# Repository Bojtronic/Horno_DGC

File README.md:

# 🔥 Sistema de Automatización para Horno Eléctrico

El sistema ha sido desarrollado utilizando **ESP32, diseño de PCB en KiCad y una interfaz web**, permitiendo la **supervisión de sensores y control de actuadores en tiempo real**.

Este documento describe paso a paso cómo configurar el entorno de desarrollo, entender la arquitectura del sistema y ejecutar la aplicación.

El proyecto se encuentra en una etapa inicial y toma como referencia el Trabajo Final de Graduación (TFG) de Manuel Bojorge.

---

## 📦 Requisitos

### Hardware
- **ESP32**
- PCB diseñado en **KiCad**
- Sensores:
  - Temperatura
  - Corriente
  - Señales analógicas (voltaje DC variable)
- Actuadores:
  - Relés (contactos secos)
  - Etapa de potencia con IGBT (PWM)

---

### Software

#### 🔹 Arduino IDE
Entorno para programar el ESP32.

Verificar instalación:
```bash
arduino --version
```

Descarga: https://www.arduino.cc/en/software

---

#### 🔹 KiCad
Software para diseño de esquemas y PCB.

Descarga: https://www.kicad.org/

---

#### 🔹 Visual Studio Code
Editor recomendado para:
- Edición de código
- Control de versiones
- Manejo del proyecto

Descarga: https://code.visualstudio.com/

---

#### 🔹 Git (opcional)
Para control de versiones.

Verificar:
```bash
git --version
```

Descarga: https://git-scm.com/

---

### Sistema Operativo
- **Windows 10 / 11** (recomendado)

---

## 📥 1. Estructura del Proyecto

El proyecto se divide en tres componentes principales:

| Componente | Descripción |
|----------|------------|
| Hardware (PCB) | Diseño electrónico en KiCad |
| Firmware (ESP32) | Control de entradas y salidas |
| Interfaz Web | Visualización y control remoto |

---

## 🧩 2. Diseño del Hardware (PCB)

El diseño del PCB se realiza en **KiCad** e incluye:

### 🔹 Entradas digitales
- Tipo: **contacto seco**
- Conversión a nivel lógico:
  - **3.3V → 1 lógico**
  - **< 1.7V → 0 lógico**

Permiten detectar:
- Estados ON/OFF externos
- Sensores digitales

---

### 🔹 Entradas analógicas
- Señales de **voltaje DC variable**
- Usadas para:
  - Sensores de temperatura
  - Sensores de corriente
  - Otras variables físicas

---

### 🔹 Salidas digitales (Relés)
- Control de **contactos secos**
- Permiten manejar:
  - **120 VAC**
  - **240 VAC**

Aplicaciones:
- Encendido/apagado del horno
- Control de resistencias
- Activación de sistemas auxiliares

---

### 🔹 Salidas analógicas (voltaje variable)
- Rango:
  - **0V – 3.3V DC (ESP32)**
- Amplificación:
  - Hasta **12V DC**

Estas señales se exponen en terminales del PCB para controlar:
- Drivers externos
- Módulos de potencia

---

### 🔹 Control PWM con IGBT
- Generación de señal **PWM desde el ESP32**
- Etapa de potencia:
  - Driver de **IGBT**
- Permite:
  - Control fino de potencia del horno
  - Regulación de temperatura

---

## 🧠 3. Arquitectura del Sistema

El sistema funciona bajo el siguiente flujo:

1. La **interfaz web** envía comandos
2. El **ESP32 recibe las solicitudes**
3. El microcontrolador:
   - Procesa entradas
   - Controla salidas
4. Se actualizan los valores en la interfaz

---

## 🌐 4. Interfaz Web

La aplicación web permite:

### 🔹 Monitoreo
- Temperatura
- Corriente
- Voltajes
- Estados digitales

---

### 🔹 Control
- Activación/desactivación de relés
- Control de salidas analógicas
- Ajuste de parámetros de operación

---

### 🔹 Comunicación
- La interfaz envía comandos al ESP32
- El ESP32 responde con datos en tiempo real

---

## ⚙️ 5. Programación del ESP32

Abrir el proyecto en **Arduino IDE**

Seleccionar:
- Placa: ESP32
- Puerto correspondiente

Compilar y cargar:

```bash
Upload
```

El firmware se encarga de:

- Leer entradas digitales y analógicas
- Generar señales PWM
- Controlar relés
- Comunicarse con la interfaz web

---

## ▶️ 6. Ejecución del Sistema

1. Energizar el PCB
2. Conectar el ESP32 a la red
3. Acceder a la interfaz web (según configuración de red)

Desde la interfaz se puede:

- Ver datos en tiempo real
- Controlar el horno
- Ajustar parámetros

---

## 🏗 7. Flujo de Desarrollo

### 🔹 Hardware
- Diseño esquemático en KiCad
- Diseño de PCB
- Fabricación y pruebas

---

### 🔹 Firmware
- Desarrollo en Arduino IDE
- Pruebas de entradas/salidas
- Integración con hardware

---

### 🔹 Software
- Desarrollo de interfaz web
- Integración con ESP32
- Pruebas de comunicación

---

## 🛡 Reglas importantes

- ❌ No conectar cargas AC sin aislamiento adecuado
- ❌ No exceder voltajes de entrada del ESP32 (3.3V)
- ❌ Verificar conexiones antes de energizar

- ⚠ Manejar con precaución:
  - 120 VAC / 240 VAC
  - Etapas de potencia con IGBT

---

## 🚧 Estado del proyecto

- ✔ Diseño conceptual
- ✔ Definición de arquitectura
- ⚠ En desarrollo:
  - PCB
  - Firmware
  - Interfaz web

---

## 📌 Notas adicionales

Este proyecto toma como base el **TFG de Manuel Bojorge**, el cual sirve como referencia para:

- Arquitectura del sistema
- Diseño electrónico
- Integración hardware–software

---

## 📧 Soporte

Correo: **bojtronic@gmail.com**

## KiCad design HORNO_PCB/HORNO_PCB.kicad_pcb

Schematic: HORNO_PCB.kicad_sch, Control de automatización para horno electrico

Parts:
C5, C6, C8, C9: 10nF; C_Disc_D5.1mm_W3.2mm_P5.00mm
C7, C10: 100nF; C_Disc_D5.1mm_W3.2mm_P5.00mm
D1, D2, D3, D4, D9, D10, D11, D12, D13, D14: LED; LED_D4.0mm
F1: Fuse; Fuseholder_Cylinder-5x20mm_Schurter_0031_8201_Horizontal_Op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
Fuente_1: 12VDC; step_source
Fuente_2: 5VDC; step_source
Fuente_3: 3.3VDC; step_source
Fuente_4: -12VDC; step_source
J0_1: Alimentacion dispositivo serial; TerminalBlock_Phoenix_PT-1,5-3-5.0-H_1x03_P5.00mm_Horizontal
J0_2, J0_3, J0_4, J0_5, J0_6, J0_7, J0_8, J0_9, J0_10, J0_11, J0_12, J0_13, J0_14, J0_15, J0_16, J0_17, J0_18, J0_19: Terminales de tornillo espaciados en 5mm; TerminalBlock_Phoenix_PT-1,5-3-5.0-H_1x03_P5.00mm_Horizontal
J1: +5V +24V; TerminalBlock_MetzConnect_360271_1x01_Horizontal_ScrewM3.0_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
J7: 24VDC; TerminalBlock_Phoenix_PT-1,5-3-5.0-H_1x03_P5.00mm_Horizontal
J24, J25, J26, J27: Screw_Terminal_01x20; PinHeader_1x20_P2.54mm_Vertical
K1, K9: Relay 1; Relay_SPDT_Fujitsu_FTR-LYCA005x_FormC_Vertical
K2, K8: Relay 2; Relay_SPDT_Fujitsu_FTR-LYCA005x_FormC_Vertical
K7: Relay 3; Relay_SPDT_Fujitsu_FTR-LYCA005x_FormC_Vertical
Q1, Q2: 2N2222; TO-92
Q6, Q7: IRG4PF50W; TO-247-3_Vertical
R1, R2, R3, R4, R20, R26: 270Ω - 1/4 W; R_Axial_DIN0207_L6.3mm_D2.5mm_P10.16mm_Horizontal
R5, R6: 1 W; R_Axial_DIN0411_L9.9mm_D3.6mm_P15.24mm_Horizontal
R7, R8, R12, R28: 2.4 KΩ - 1/2 W; R_Axial_DIN0309_L9.0mm_D3.2mm_P15.24mm_Horizontal
R9, R10, R11, R44, R46, R48: 1 kΩ - 1/4 W; R_Axial_DIN0207_L6.3mm_D2.5mm_P10.16mm_Horizontal
R13, R16, R17, R18, R21, R22, R23, R24, R27, R29: Depende de la aplicación salida analógica; R_Axial_DIN0207_L6.3mm_D2.5mm_P10.16mm_Horizontal
R14, R15: 7.5KΩ - 1/4 W; R_Axial_DIN0207_L6.3mm_D2.5mm_P10.16mm_Horizontal
R19, R25: 10Ω - 1/4 W; R_Axial_DIN0207_L6.3mm_D2.5mm_P10.16mm_Horizontal
R37, R38: 39Ω - 1/4 W; R_Axial_DIN0207_L6.3mm_D2.5mm_P10.16mm_Horizontal
U1, U2, U3, U4: TLP521-1; DIP-4_W7.62mm
U9, U10, U17, U18: LM741; LM741_TH
U15, U19: TLP250; DIP-8_W7.62mm
U25: UDN2981A; DIP-18_W7.62mm_LongPads

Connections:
unnamed: D1.2 (A), R28.2
unnamed: D1.1 (K), U1.1
unnamed: D2.2 (A), R7.2
unnamed: D2.1 (K), U2.1
unnamed: D3.2 (A), R8.2
unnamed: D3.1 (K), U3.1
unnamed: D4.2 (A), R12.2
unnamed: D4.1 (K), U4.1
unnamed: D9.2 (A), R29.1
unnamed: D10.2 (A), R27.1
unnamed: C5.2, C6.2, C8.2, C9.2, C10.2, D9.1 (K), D10.1 (K), D11.1 (K), D12.1 (K), D13.1 (K), D14.1 (K), Fuente_1.2 (IN-), Fuente_1.3 (OUT-), Fuente_2.2 (IN-), Fuente_2.3 (OUT-), Fuente_3.2 (IN-), Fuente_3.3 (OUT-), Fuente_4.3 (OUT-), J0_5.3, J0_10.3, J0_13.2, J0_14.3, J0_18.3, J7.3, J25.20, K1.A2, K2.A2, K7.A2, K8.A2, K9.A2, Q6.3 (E), Q7.3 (E), R21.2, R23.2, R37.2, R38.2, U1.2, U1.3, U2.2, U2.3, U3.2, U3.3, U4.2, U4.3, U15.3 (C), U19.3 (C), U25.10 (GND)
unnamed: D11.2 (A), R18.1
unnamed: D12.2 (A), R17.1
unnamed: D13.2 (A), R16.1
unnamed: D14.2 (A), R13.1
unnamed: F1.1, Fuente_1.1 (IN+), Fuente_2.1 (IN+), Fuente_3.1 (IN+), J0_2.3, J0_11.3, J0_12.3, J0_15.3, U25.9 (Vs)
unnamed: Fuente_1.4 (OUT+), U9.7 (V+), U10.7 (V+), U15.8 (VCC), U17.7 (V+), U18.7 (V+), U19.8 (VCC)
unnamed: Fuente_2.4 (OUT+), J24.2, J25.19
unnamed: Fuente_3.4 (OUT+), J26.5, J26.11, J26.17, Q1.3 (C), Q2.3 (C), R1.2, R2.2, R3.2, R4.2
unnamed: Fuente_4.4 (OUT+), U9.4 (V-), U10.4 (V-), U15.5 (VEE), U17.4 (V-), U18.4 (V-), U19.5 (VEE)
unnamed: J0_1.1, J0_1.2, J0_1.3, J1.1
unnamed: J0_2.1, R28.1
unnamed: J0_3.1, J24.5
unnamed: J0_3.2, J24.6
unnamed: C7.2, J0_3.3, J24.1
unnamed: J0_4.1, K1.12
unnamed: J0_4.2, K1.11
unnamed: J0_4.3, K1.14
unnamed: C6.1, J0_5.1, U9.3 (+)
unnamed: C5.1, J0_5.2, U10.3 (+)
unnamed: J0_6.1, K2.12
unnamed: J0_6.2, K2.11
unnamed: J0_6.3, K2.14
unnamed: J0_7.1, K9.12
unnamed: J0_7.2, K9.11
unnamed: J0_7.3, K9.14
unnamed: J0_8.1, K8.12
unnamed: J0_8.2, K8.11
unnamed: J0_8.3, K8.14
unnamed: J0_9.1, K7.12
unnamed: J0_9.2, K7.11
unnamed: J0_9.3, K7.14
unnamed: J0_10.1, R29.2, U25.18 (O1)
unnamed: J0_11.1, R7.1
unnamed: J0_12.1, R8.1
unnamed: J0_13.1, R24.1, U18.6
unnamed: J0_13.3, R22.1, U17.6
unnamed: J0_14.1, Q7.2 (C), R6.2
unnamed: J0_14.2, R6.1
unnamed: J0_15.1, R12.1
unnamed: J0_16.1, J27.17
unnamed: J0_16.3, J27.19
unnamed: J0_17.1, J27.11
unnamed: J0_17.3, J27.13
unnamed: J0_18.1, Q6.2 (C), R5.2
unnamed: J0_18.2, R5.1
unnamed: J0_19.1, J27.5
unnamed: J0_19.3, J27.7
unnamed: F1.2, J7.1
unnamed: C7.1, J24.3
unnamed: J24.4, J26.4, J26.10, J26.16
unnamed: J24.9, J26.8
unnamed: J24.10, J26.3, J26.9, J26.15
unnamed: J24.11, J26.14
unnamed: J24.12, J26.1, J26.7, J26.13
unnamed: J24.13, R11.2
unnamed: J24.15, R9.2
unnamed: J24.16, R10.2
unnamed: J24.17, R26.2
unnamed: J24.18, R20.2
unnamed: J25.3, J26.2
unnamed: J25.4, R46.2
unnamed: J25.5, R44.2
unnamed: J25.6, R48.2
unnamed: C9.1, J25.8, U18.3 (+)
unnamed: C8.1, J25.9, U17.3 (+)
unnamed: J25.10, Q2.1 (E), R37.1
unnamed: J25.11, Q1.1 (E), R38.1
unnamed: J25.12, R2.1, U2.4
unnamed: J25.13, R1.1, U1.4
unnamed: J25.14, R4.1, U4.4
unnamed: J25.17, R3.1, U3.4
unnamed: C10.1, J25.18
unnamed: Q1.2 (B), R14.1
unnamed: Q2.2 (B), R15.1
unnamed: Q6.1 (G), R19.1
unnamed: Q7.1 (G), R25.1
unnamed: R19.2, U15.7 (VO)
unnamed: R25.2, U19.7 (VO)
unnamed: R14.2, U9.2 (-), U9.6
unnamed: R15.2, U10.2 (-), U10.6
unnamed: R20.1, U15.2 (A)
unnamed: R21.1, R22.2, U17.2 (-)
unnamed: R23.1, R24.2, U18.2 (-)
unnamed: R26.1, U19.2 (A)
unnamed: R48.1, U25.1 (I1)
unnamed: R46.1, U25.2 (I2)
unnamed: R44.1, U25.3 (I3)
unnamed: R11.1, U25.4 (I4)
unnamed: R10.1, U25.5 (I5)
unnamed: R9.1, U25.6 (I6)
unnamed: K7.A1, R27.2, U25.17 (O2)
unnamed: K8.A1, R18.2, U25.16 (O3)
unnamed: K9.A1, R17.2, U25.15 (O4)
unnamed: K2.A1, R16.2, U25.14 (O5)
unnamed: K1.A1, R13.2, U25.13 (O6)

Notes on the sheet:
NC IN1POS NC IN1NEG NC NC NC IN2POS NC IN2NEG NC NC NC IN3POS NC IN3NEG NC NC NC NC
24 VDC
3.3 VDC
-12 voltios
GND 5V 3.3V P36 P37 P38 P39 P34 P35 P32 P33 P25 P26 P27 P14 P12 P13 P21
Dispositivo serial
3.3 voltios
+12 voltios
5 VDC
SCK1 CS1 SO1 GND VCC NC SCK2 CS2 SO2 GND VCC NC SCK3 CS3 SO3 GND VCC NC NC NC
0-10 voltios
GND 5V 3.3V GND RX TX RST P0 P22 P19 P23 P18 P5 P15 P2 P4 P17 P16

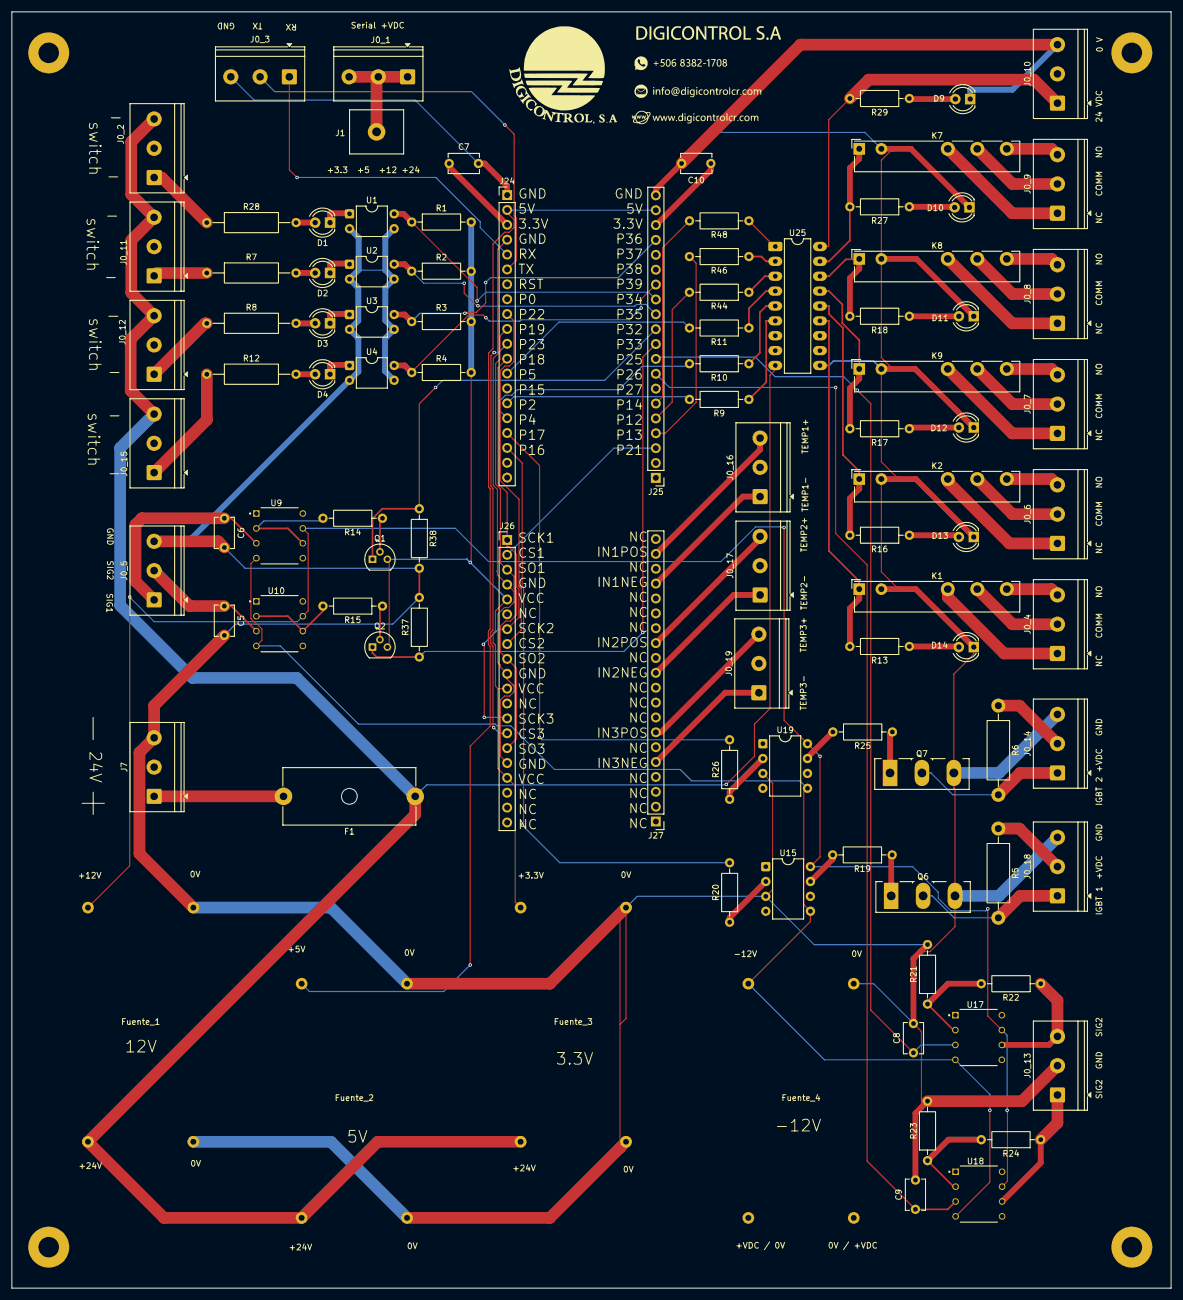
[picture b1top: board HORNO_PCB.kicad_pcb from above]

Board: 2 copper layers, 198.0 x 218.0 mm, 104 parts (0 on the bottom side), 106 nets.

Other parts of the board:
MH1, MH2, MH3, MH4: MountingHole_3.5mm_Pad

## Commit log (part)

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2026-04-03 Proycto base (obtenido del TFG)
2026-04-04 Base del proyecto
2026-04-13 Modificando salida de relé
2026-05-17 Salidas con inversor CMOS 4069 y ULN2803
2026-05-17 Interfaces digitales de entrada y salida: corregidas
2026-06-28 Cambios al esquematico y carpeta con datasheets
